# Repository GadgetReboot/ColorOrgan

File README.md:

# ColorOrgan
Color Organ using transistors with low, mid, and high open collector outputs

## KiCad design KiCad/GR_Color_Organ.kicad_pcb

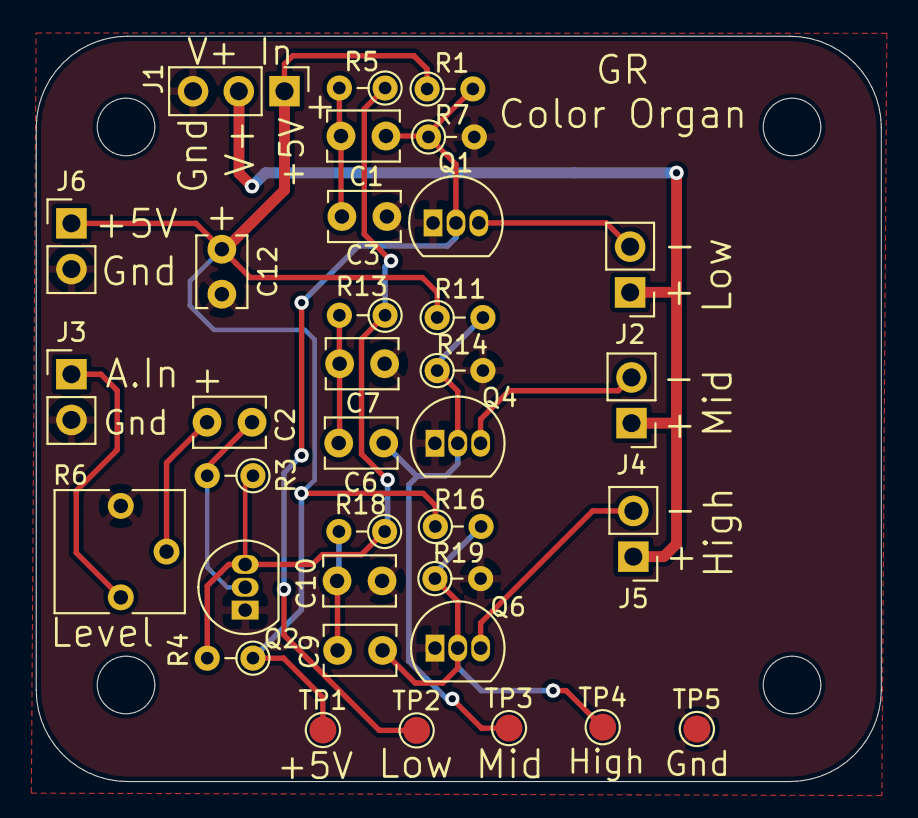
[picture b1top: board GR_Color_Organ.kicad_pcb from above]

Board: 2 copper layers, 46.9 x 41.4 mm, 39 parts (0 on the bottom side), 16 nets.

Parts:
C1: 2.2uF; C_Disc_D3.8mm_W2.6mm_P2.50mm
C2: 1uF; C_Disc_D3.8mm_W2.6mm_P2.50mm
C3: 220nF; C_Disc_D3.8mm_W2.6mm_P2.50mm
C6: 15nF; C_Disc_D3.8mm_W2.6mm_P2.50mm
C7: 33nF; C_Disc_D3.8mm_W2.6mm_P2.50mm
C9: 1.5nF; C_Disc_D3.8mm_W2.6mm_P2.50mm
C10: 1nF; C_Disc_D3.8mm_W2.6mm_P2.50mm
C12: 4.7uF; C_Disc_D3.8mm_W2.6mm_P2.50mm
J1: Conn_01x03; PinHeader_1x03_P2.54mm_Vertical
J2, J3, J4, J5, J6: Conn_01x02; PinHeader_1x02_P2.54mm_Vertical
MH1, MH2, MH3, MH4: MountingHole; MountingHole_3.2mm_M3
Q1, Q2, Q4, Q6: 2N3904; TO-92_Inline
R1, R11, R16: 100K; R_Axial_DIN0204_L3.6mm_D1.6mm_P2.54mm_Vertical
R3: 47K; R_Axial_DIN0204_L3.6mm_D1.6mm_P2.54mm_Vertical
R4, R5, R7, R13, R14, R18, R19: 10K; R_Axial_DIN0204_L3.6mm_D1.6mm_P2.54mm_Vertical
R6: 10K; Potentiometer_Vishay_T73YP_Vertical
TP1, TP2, TP3, TP4, TP5: TestPoint; TestPoint_Pad_D1.5mm

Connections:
+5V: C12.1, J1.1, J6.1, R1.1, R4.1, R11.1, R16.1, TP1.1
/High: C9.1, Q6.2, R16.2, R19.1, TP4.1
/High_Out: J5.2, Q6.3
/Input: J3.1, R6.1
/Low: C1.1, Q1.2, R1.2, R7.1, TP2.1
/Low_Out: J2.2, Q1.3
/Mid: C6.1, Q4.2, R11.2, R14.1, TP3.1
/Mid_Out: J4.2, Q4.3
/V+: J1.2, J2.1, J4.1, J5.1
GNDREF: C3.2, C7.2, C10.2, C12.2, J1.3, J3.2, J6.2, Q1.1, Q2.1, Q4.1, Q6.1, R6.3, R7.2, R14.2, R19.2, TP5.1
unnamed: C1.2, C3.1, R5.2
unnamed: C2.1, Q2.2, R3.2
unnamed: C2.2, R6.2
unnamed: C6.2, C7.1, R13.2
unnamed: C9.2, C10.1, R18.2
unnamed: Q2.3, R3.1, R4.2, R5.1, R13.1, R18.1
